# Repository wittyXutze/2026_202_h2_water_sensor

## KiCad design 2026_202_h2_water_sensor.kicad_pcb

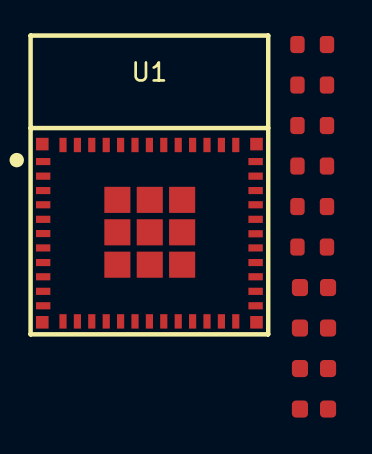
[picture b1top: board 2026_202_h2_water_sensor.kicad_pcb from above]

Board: 2 copper layers, 11 parts (0 on the bottom side), 4 nets, no tracks yet.

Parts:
C6: 4.7uF; C_0603
C7, C8, C9: 100nF; C_0603
R8, R9: 10Ω; R_0603
R10, R11: 100Ω; R_0603
R12, R13: 10kΩ; R_0603
U1: ESP32-H2-MINI-1-N4; WIFIM-SMD_61P-L16.6-W13.2-P0.80-ESP32-C6-MINI-1-N4

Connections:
/ESP32-H2/EN: C8.1, R13.2
/ESP32-H2/IO0: C9.1, R12.2
/ESP32-H2/VCC_ESP: C6.1, C7.1, R12.1, R13.1
GND: C6.2, C7.2, C8.2, C9.2, R10.2, R11.2, U1.1 (GND), U1.39 (GND), U1.40 (GND), U1.41 (GND), U1.42 (GND), U1.43 (GND), U1.44 (GND), U1.45 (GND), U1.46 (GND), U1.47 (GND), U1.48 (GND), U1.49 (GND), U1.50 (GND), U1.51 (GND), U1.52 (GND), U1.53 (GND)
